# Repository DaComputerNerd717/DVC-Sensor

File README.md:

# DVC-Sensor
UMD 2023 senior design deer detection project\
Arduino nano source code: deerdetionsensorarray.ino

This project was inspired by the large amount of damage caused by deer-vehicle collisions in Michigan. Our state has a large amount of deer, and any car that runs into a deer has a good chance to be totalled. This project aims to reduce deer collisions by providing detection modules and lights to notify drivers about deer approaching the road. 

So far, we have detection modules based on image processing, which do successfully detect deer. Two variations exist; one variation uses a Raspberry Pi for the image processing, and one uses an Arduino Nano instead. Some software has also been created to control the module, as well. 

A light module has also been created, in order to simplify the process of blinking a light and driving LEDs. The module is also designed with expansion in mind, with documentation including a possible way to use a diode and relay to drive more powerful or higher voltage lights. The schematics for the lighting module have been provided in the form of images in documentation, and KiCad project files. 

The project still needs more work to be done. One major point is improving the accuracy of the detector modules. The Pi version is overall more accurate, but neither are quite good enough. Furthermore, we have not tested either of these modules at scale, having only built one of each.

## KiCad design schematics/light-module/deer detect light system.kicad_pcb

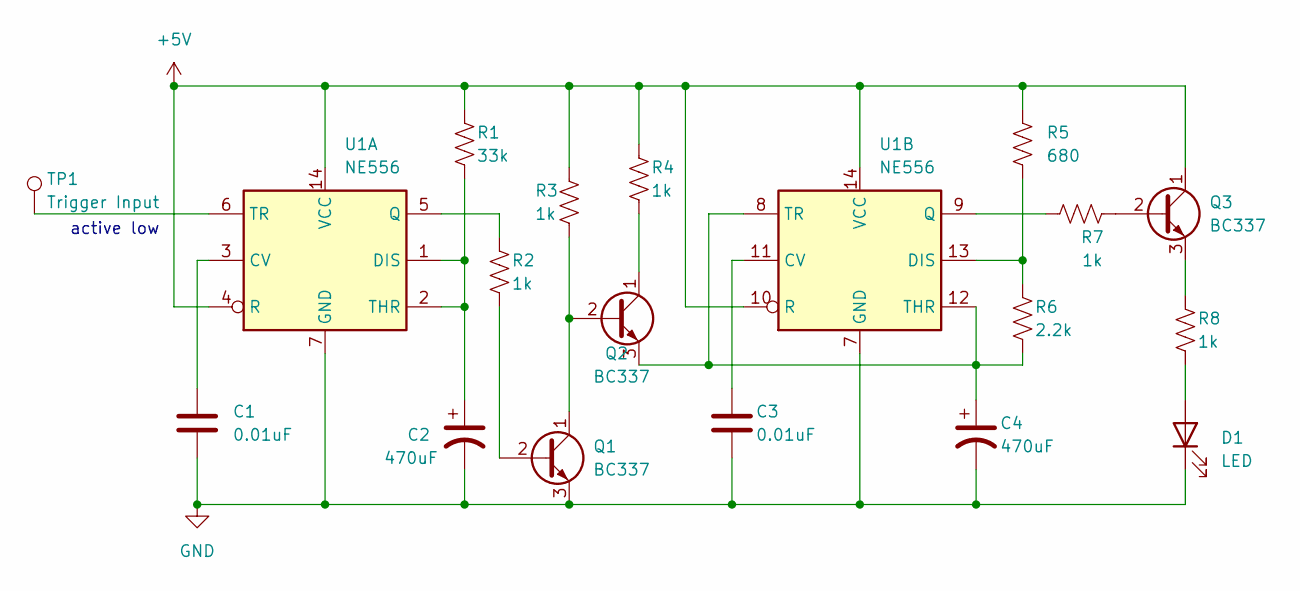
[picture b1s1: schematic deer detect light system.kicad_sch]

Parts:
C1, C3: 0.01uF
C2, C4: 470uF
D1: LED; LED_D5.0mm_IRBlack
Q1, Q2, Q3: BC337; TO-92_Inline
R1: 33k
R2, R3, R4, R7, R8: 1k
R5: 680
R6: 2.2k
TP1: Trigger Input
U1: NE556

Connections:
+5V: Q3.1 (C), R1.1, R3.1, R4.1, R5.1, U1.4 (R), U1.10 (R), U1.14 (VCC)
GND: C1.2, C2.2, C3.2, C4.2, D1.1 (K), Q1.3 (E), U1.7 (GND)
unnamed: C1.1, U1.3 (CV)
unnamed: C2.1, R1.2, U1.1 (DIS), U1.2 (THR)
unnamed: C3.1, U1.11 (CV)
unnamed: C4.1, Q2.3 (E), R6.2, U1.8 (TR), U1.12 (THR)
unnamed: D1.2 (A), R8.2
unnamed: Q1.1 (C), Q2.2 (B), R3.2
unnamed: Q1.2 (B), R2.2
unnamed: Q2.1 (C), R4.2
unnamed: Q3.2 (B), R7.2
unnamed: Q3.3 (E), R8.1
unnamed: R2.1, U1.5 (Q)
unnamed: R5.2, R6.1, U1.13 (DIS)
unnamed: R7.1, U1.9 (Q)
unnamed: TP1.1, U1.6 (TR)

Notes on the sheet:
active low

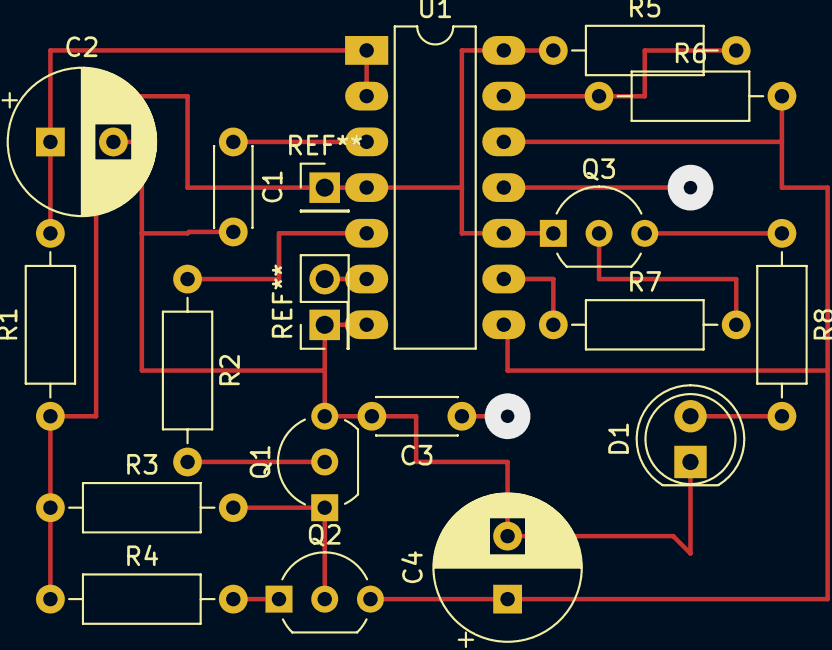
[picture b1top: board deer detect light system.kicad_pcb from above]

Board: 2 copper layers, 17 parts (0 on the bottom side), 15 nets.

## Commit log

2023-12-03 Add light module schematic files
    These files are meant to be opened with KiCad version 6. Any older version of KiCad may not work.
2023-12-05 Add documentation for light module
2024-08-11 Update README.md
    Added description of project, current achievements, and work to be done to README
